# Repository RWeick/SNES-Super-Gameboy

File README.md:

# SNES-Super-Gameboy
The Kicad files for the SNES NTSC Super Gameboy

PCB Thickness: 1.2 mm

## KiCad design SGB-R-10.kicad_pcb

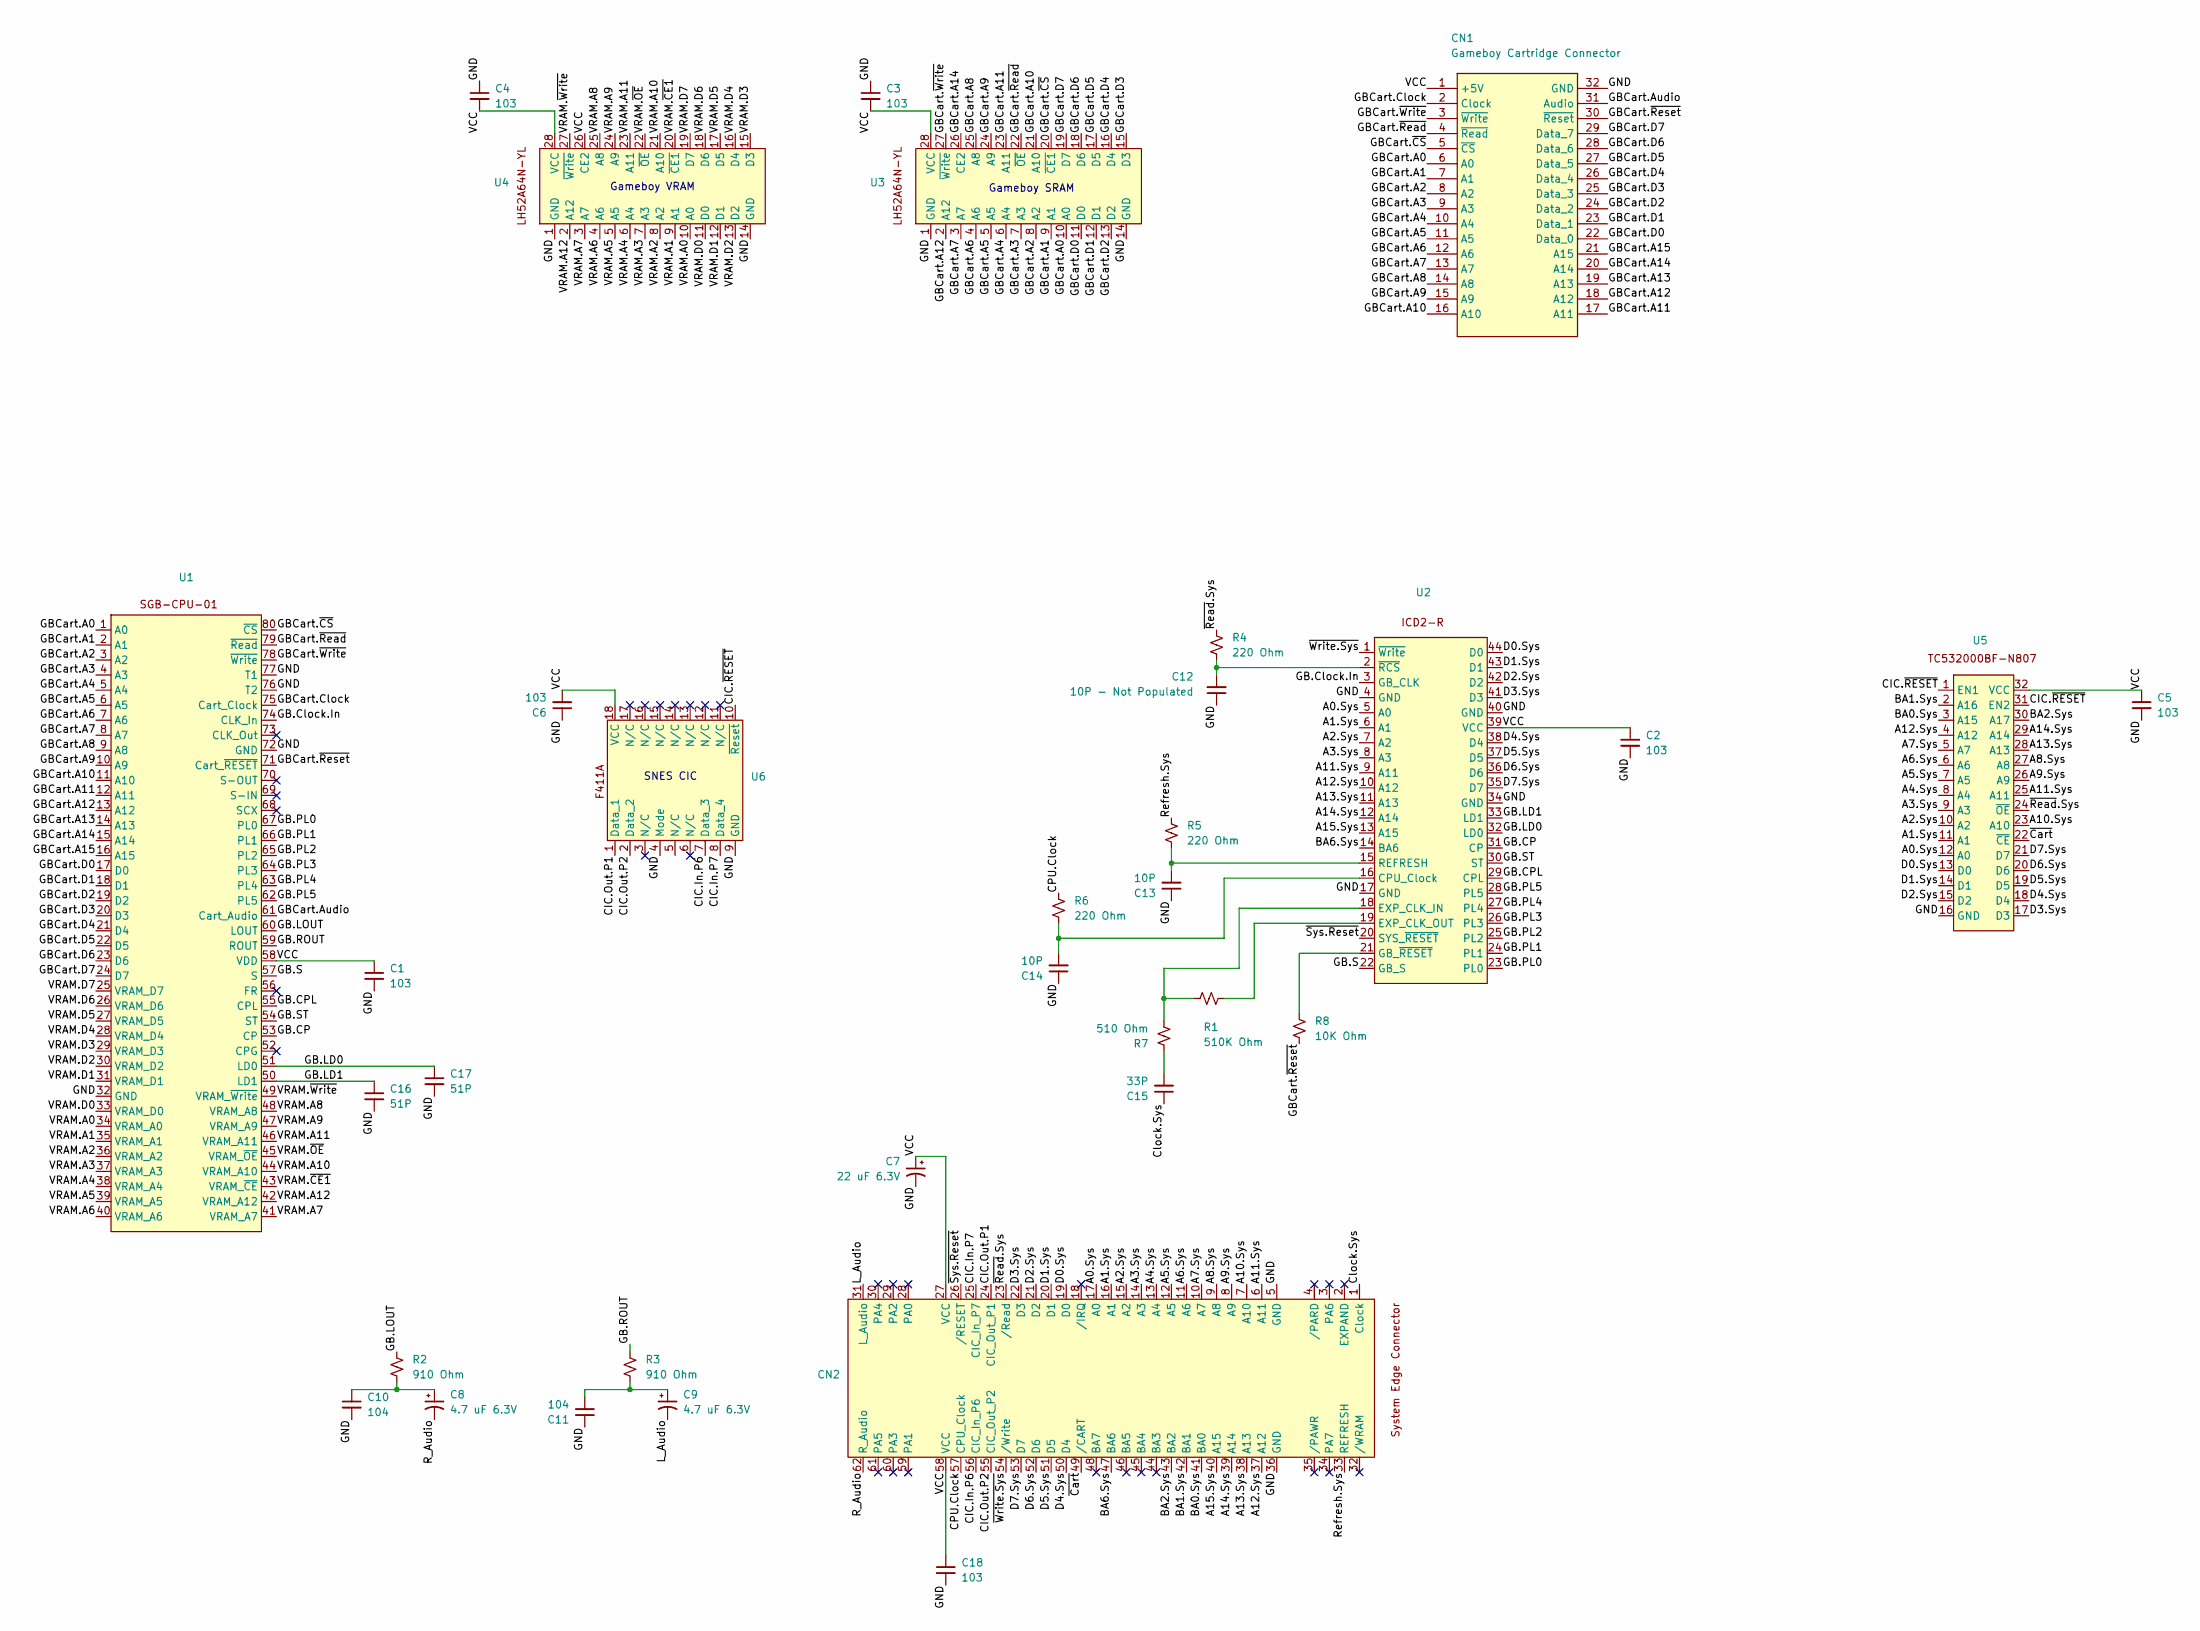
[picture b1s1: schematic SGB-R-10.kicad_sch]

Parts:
C1, C2, C3, C4, C5, C6, C18: 103; 0805 SMD
C7: 22 uF 6.3V; Electrolytic Cap
C8, C9: 4.7 uF 6.3V; Electrolytic Cap
C10, C11: 104; 0805 SMD
C12: 10P - Not Populated; 0805 SMD
C13, C14: 10P; 0805 SMD
C15: 33P; 0805 SMD
C16, C17: 51P; 0805 SMD
CN1: Gameboy Cartridge Connector; GB Cartridge Slot
CN2: Edge Connector
R1: 510K Ohm; 0805 SMD
R2, R3: 910 Ohm; 0805 SMD
R4, R5, R6: 220 Ohm; 0805 SMD
R7: 510 Ohm; 0805 SMD
R8: 10K Ohm; 0805 SMD
U1: CPU SGB
U2: ICD2-R
U3, U4: LH52A64N SRAM
U5: SYS-SGB-2 ROM
U6: F411A CIC

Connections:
/A0.Sys: CN2.17 (A0), U2.5 (A0), U5.12 (A0)
/A1.Sys: CN2.16 (A1), U2.6 (A1), U5.11 (A1)
/A2.Sys: CN2.15 (A2), U2.7 (A2), U5.10 (A2)
/A3.Sys: CN2.14 (A3), U2.8 (A3), U5.9 (A3)
/A4.Sys: CN2.13 (A4), U5.8 (A4)
/A5.Sys: CN2.12 (A5), U5.7 (A5)
/A6.Sys: CN2.11 (A6), U5.6 (A6)
/A7.Sys: CN2.10 (A7), U5.5 (A7)
/A8.Sys: CN2.9 (A8), U5.27 (A8)
/A9.Sys: CN2.8 (A9), U5.26 (A9)
/A10.Sys: CN2.7 (A10), U5.23 (A10)
/A11.Sys: CN2.6 (A11), U2.9 (A11), U5.25 (A11)
/A12.Sys: CN2.37 (A12), U2.10 (A12), U5.4 (A12)
/A13.Sys: CN2.38 (A13), U2.11 (A13), U5.28 (A13)
/A14.Sys: CN2.39 (A14), U2.12 (A14), U5.29 (A14)
/A15.Sys: CN2.40 (A15), U2.13 (A15)
/BA0.Sys: CN2.41 (BA0), U5.3 (A15)
/BA1.Sys: CN2.42 (BA1), U5.2 (A16)
/BA2.Sys: CN2.43 (BA2), U5.30 (A17)
/BA6.Sys: CN2.47 (BA6), U2.14 (BA6)
/CIC.In.P6: CN2.56 (CIC_In_P6), U6.7 (Data_3)
/CIC.In.P7: CN2.25 (CIC_In_P7), U6.8 (Data_4)
/CIC.Out.P1: CN2.24 (CIC_Out_P1), U6.1 (Data_1)
/CIC.Out.P2: CN2.55 (CIC_Out_P2), U6.2 (Data_2)
/CIC.~RESET: U5.1 (EN1), U5.31 (EN2), U6.10 (~Reset)
/CPU.Clock: CN2.57 (CPU_Clock), R6.1
/Clock.Sys: C15.1, CN2.1 (Clock)
/D0.Sys: CN2.19 (D0), U2.44 (D0), U5.13 (D0)
/D1.Sys: CN2.20 (D1), U2.43 (D1), U5.14 (D1)
/D2.Sys: CN2.21 (D2), U2.42 (D2), U5.15 (D2)
/D3.Sys: CN2.22 (D3), U2.41 (D3), U5.17 (D3)
/D4.Sys: CN2.50 (D4), U2.38 (D4), U5.18 (D4)
/D5.Sys: CN2.51 (D5), U2.37 (D5), U5.19 (D5)
/D6.Sys: CN2.52 (D6), U2.36 (D6), U5.20 (D6)
/D7.Sys: CN2.53 (D7), U2.35 (D7), U5.21 (D7)
/GB.CP: U1.53 (CP), U2.31 (CP)
/GB.CPL: U1.55 (CPL), U2.29 (CPL)
/GB.Clock.In: U1.74 (CLK_In), U2.3 (GB_CLK)
/GB.LD0: C17.1, U1.51 (LD0), U2.32 (LD0)
/GB.LD1: C16.1, U1.50 (LD1), U2.33 (LD1)
/GB.LOUT: R2.1, U1.60 (LOUT)
/GB.PL0: U1.67 (PL0), U2.23 (PL0)
/GB.PL1: U1.66 (PL1), U2.24 (PL1)
/GB.PL2: U1.65 (PL2), U2.25 (PL2)
/GB.PL3: U1.64 (PL3), U2.26 (PL3)
/GB.PL4: U1.63 (PL4), U2.27 (PL4)
/GB.PL5: U1.62 (PL5), U2.28 (PL5)
/GB.ROUT: R3.1, U1.59 (ROUT)
/GB.S: U1.57 (S), U2.22 (GB_S)
/GB.ST: U1.54 (ST), U2.30 (ST)
/GBCart.A0: CN1.6 (A0), U1.1 (A0), U3.10 (A0)
/GBCart.A1: CN1.7 (A1), U1.2 (A1), U3.9 (A1)
/GBCart.A2: CN1.8 (A2), U1.3 (A2), U3.8 (A2)
/GBCart.A3: CN1.9 (A3), U1.4 (A3), U3.7 (A3)
/GBCart.A4: CN1.10 (A4), U1.5 (A4), U3.6 (A4)
/GBCart.A5: CN1.11 (A5), U1.6 (A5), U3.5 (A5)
/GBCart.A6: CN1.12 (A6), U1.7 (A6), U3.4 (A6)
/GBCart.A7: CN1.13 (A7), U1.8 (A7), U3.3 (A7)
/GBCart.A8: CN1.14 (A8), U1.9 (A8), U3.25 (A8)
/GBCart.A9: CN1.15 (A9), U1.10 (A9), U3.24 (A9)
/GBCart.A10: CN1.16 (A10), U1.11 (A10), U3.21 (A10)
/GBCart.A11: CN1.17 (A11), U1.12 (A11), U3.23 (A11)
/GBCart.A12: CN1.18 (A12), U1.13 (A12), U3.2 (A12)
/GBCart.A13: CN1.19 (A13), U1.14 (A13)
/GBCart.A14: CN1.20 (A14), U1.15 (A14), U3.26 (CE2)
/GBCart.A15: CN1.21 (A15), U1.16 (A15)
/GBCart.Audio: CN1.31 (Audio), U1.61 (Cart_Audio)
/GBCart.Clock: CN1.2 (Clock), U1.75 (Cart_Clock)
/GBCart.D0: CN1.22 (Data_0), U1.17 (D0), U3.11 (D0)
/GBCart.D1: CN1.23 (Data_1), U1.18 (D1), U3.12 (D1)
/GBCart.D2: CN1.24 (Data_2), U1.19 (D2), U3.13 (D2)
/GBCart.D3: CN1.25 (Data_3), U1.20 (D3), U3.15 (D3)
/GBCart.D4: CN1.26 (Data_4), U1.21 (D4), U3.16 (D4)
/GBCart.D5: CN1.27 (Data_5), U1.22 (D5), U3.17 (D5)
/GBCart.D6: CN1.28 (Data_6), U1.23 (D6), U3.18 (D6)
/GBCart.D7: CN1.29 (Data_7), U1.24 (D7), U3.19 (D7)
/GBCart.~CS: CN1.5 (~CS), U1.80 (~CS), U3.20 (~CE1)
/GBCart.~Read: CN1.4 (~Read), U1.79 (~Read), U3.22 (~OE)
/GBCart.~Reset: CN1.30 (~Reset), R8.2, U1.71 (Cart_~RESET)
/GBCart.~Write: CN1.3 (~Write), U1.78 (~Write), U3.27 (~Write)
/GND: C1.2, C2.2, C3.1, C4.1, C5.2, C6.1, C7.2, C10.2, C11.1, C12.1, C13.1, C14.1, C16.2, C17.2, C18.2, CN1.32 (GND), CN2.5 (GND), CN2.36 (GND), U1.32 (GND), U1.72 (GND), U1.76 (T2), U1.77 (T1), U2.4 (GND), U2.17 (GND), U2.34 (GND), U2.40 (GND), U3.1 (GND), U3.14 (GND), U4.1 (GND), U4.14 (GND), U5.16 (GND), U6.4 (Mode), U6.9 (GND)
/L_Audio: C9.2, CN2.31 (L_Audio)
/R_Audio: C8.2, CN2.62 (R_Audio)
/Refresh.Sys: CN2.33 (REFRESH), R5.1
/VCC: C1.1, C2.1, C3.2, C4.2, C5.1, C6.2, C7.1, C18.1, CN1.1 (+5V), CN2.27 (VCC), CN2.58 (VCC), U1.58 (VDD), U2.39 (VCC), U3.28 (VCC), U4.26 (CE2), U4.28 (VCC), U5.32 (VCC), U6.18 (VCC)
/VRAM.A0: U1.34 (VRAM_A0), U4.10 (A0)
/VRAM.A1: U1.35 (VRAM_A1), U4.9 (A1)
/VRAM.A2: U1.36 (VRAM_A2), U4.8 (A2)
/VRAM.A3: U1.37 (VRAM_A3), U4.7 (A3)
/VRAM.A4: U1.38 (VRAM_A4), U4.6 (A4)
/VRAM.A5: U1.39 (VRAM_A5), U4.5 (A5)
/VRAM.A6: U1.40 (VRAM_A6), U4.4 (A6)
/VRAM.A7: U1.41 (VRAM_A7), U4.3 (A7)
/VRAM.A8: U1.48 (VRAM_A8), U4.25 (A8)
/VRAM.A9: U1.47 (VRAM_A9), U4.24 (A9)
/VRAM.A10: U1.44 (VRAM_A10), U4.21 (A10)
/VRAM.A11: U1.46 (VRAM_A11), U4.23 (A11)
/VRAM.A12: U1.42 (VRAM_A12), U4.2 (A12)
/VRAM.D0: U1.33 (VRAM_D0), U4.11 (D0)
/VRAM.D1: U1.31 (VRAM_D1), U4.12 (D1)
/VRAM.D2: U1.30 (VRAM_D2), U4.13 (D2)
/VRAM.D3: U1.29 (VRAM_D3), U4.15 (D3)
/VRAM.D4: U1.28 (VRAM_D4), U4.16 (D4)
/VRAM.D5: U1.27 (VRAM_D5), U4.17 (D5)
/VRAM.D6: U1.26 (VRAM_D6), U4.18 (D6)
/VRAM.D7: U1.25 (VRAM_D7), U4.19 (D7)
/VRAM.~CE1: U1.43 (VRAM_~CE), U4.20 (~CE1)
/VRAM.~OE: U1.45 (VRAM_~OE), U4.22 (~OE)
/VRAM.~Write: U1.49 (VRAM_~Write), U4.27 (~Write)
/~Cart: CN2.49 (/CART), U5.22 (~CE)
/~Read.Sys: CN2.23 (/Read), R4.1, U5.24 (~OE)
/~Sys.Reset: CN2.26 (/RESET), U2.20 (SYS_~RESET)
/~Write.Sys: CN2.54 (/Write), U2.1 (~Write)
unnamed: C8.1, C10.1, R2.2
unnamed: C9.1, C11.2, R3.2
unnamed: C15.2, R7.1
unnamed: C14.2, R6.2, U2.16 (CPU_Clock)
unnamed: R1.2, R7.2, U2.18 (EXP_CLK_IN)
unnamed: R1.1, U2.19 (EXP_CLK_OUT)
unnamed: R8.1, U2.21 (GB_~RESET)
unnamed: C13.2, R5.2, U2.15 (REFRESH)
unnamed: C12.2, R4.2, U2.2 (~RCS)

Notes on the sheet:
SNES CIC
Gameboy VRAM
Gameboy SRAM

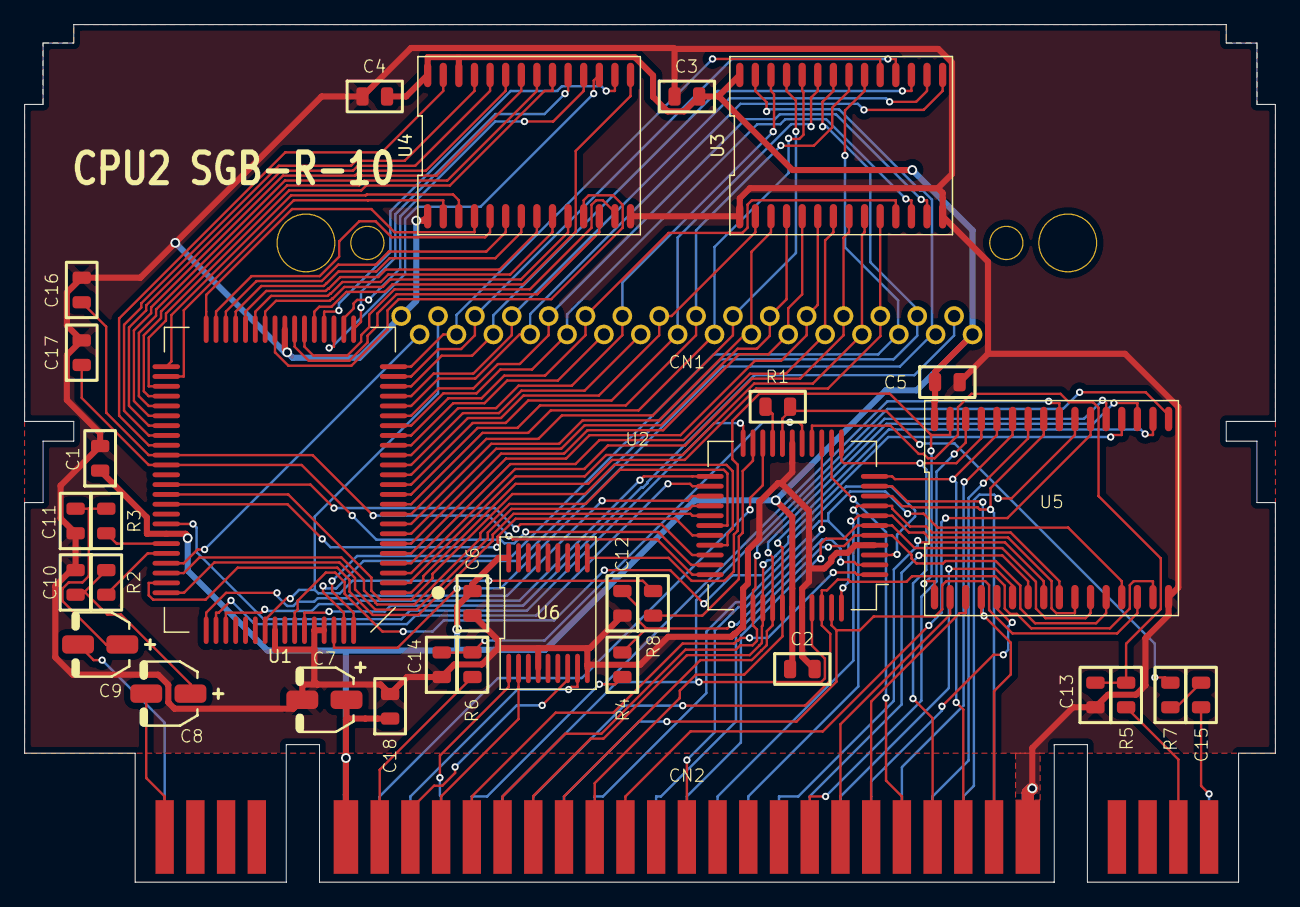
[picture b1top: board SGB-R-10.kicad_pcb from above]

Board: 2 copper layers, 101.8 x 69.8 mm, 34 parts (0 on the bottom side), 122 nets.
